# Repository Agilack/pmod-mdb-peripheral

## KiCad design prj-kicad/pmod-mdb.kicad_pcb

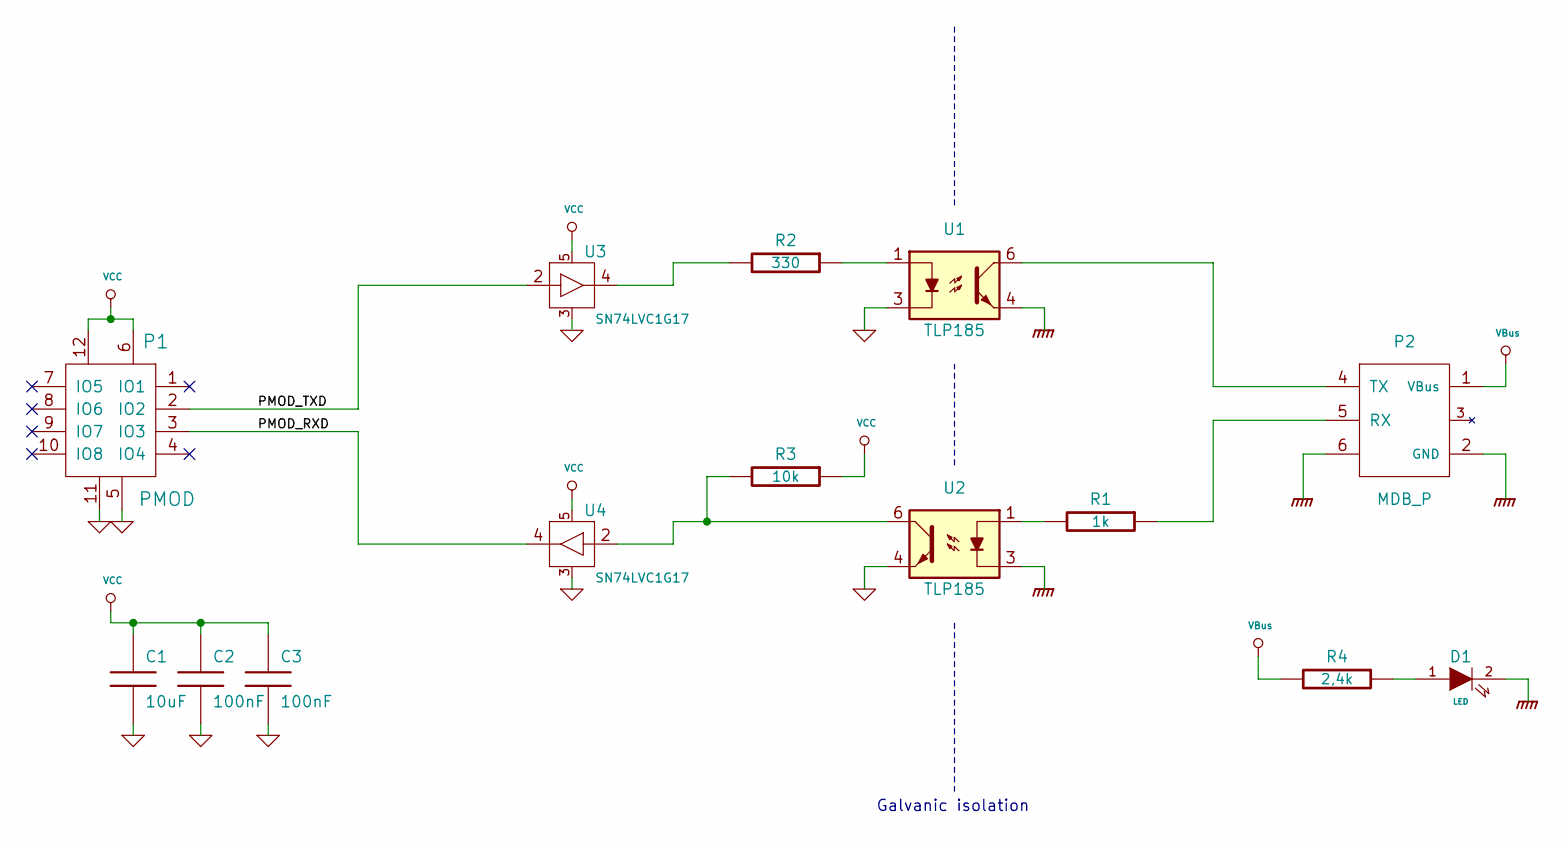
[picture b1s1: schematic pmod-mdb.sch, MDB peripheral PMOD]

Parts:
C1: 10uF; SMD0805
C2, C3: 100nF; SMD0603
D1: LED; SMD0805
P1: PMOD; CONN_PMOD-Male
P2: MDB_P; CONN_64900621122
R1: 1k; SMD0603
R2: 330; SMD0603
R3: 10k; SMD0603
R4: 2,4k; SMD0603
U1, U2: TLP185; SOP6-4
U3, U4: SN74LVC1G17; SOT23-5

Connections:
/PMOD_RXD: P1.3 (IO3), U4.4 (Y)
/PMOD_TXD: P1.2 (IO2), U3.2 (A)
GND: C1.2, C2.2, C3.2, P1.5, P1.11, U1.3, U2.4, U3.3, U4.3
GNDBUS: D1.2 (K), P2.2 (GND), P2.6, U1.4, U2.3
unnamed: D1.1 (A), R4.1
unnamed: P2.4 (TX), U1.6
unnamed: P2.5 (RX), R1.1
unnamed: R1.2, U2.1
unnamed: R2.1, U1.1
unnamed: R2.2, U3.4 (Y)
unnamed: R3.2, U2.6, U4.2 (A)
VBus: P2.1 (VBus), R4.2
VCC: C1.1, C2.1, C3.1, P1.6, P1.12, R3.1, U3.5, U4.5

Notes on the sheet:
Galvanic isolation

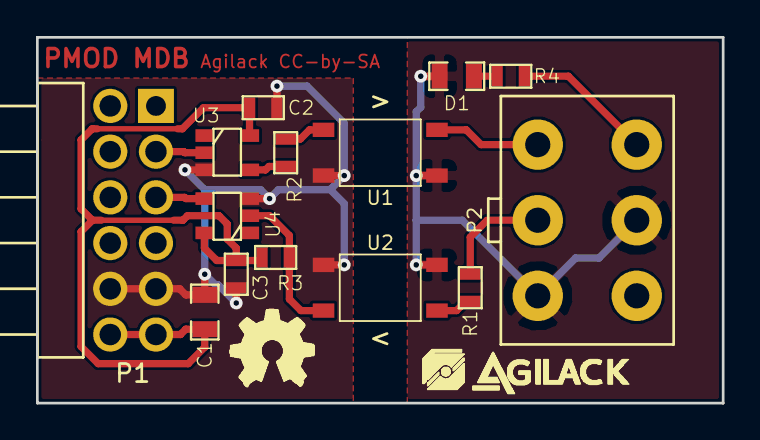
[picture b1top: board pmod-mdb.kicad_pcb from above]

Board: 2 copper layers, 38.1 x 20.3 mm, 16 parts (0 on the bottom side), 13 nets.

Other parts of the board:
agilack-11.5: 450px; logo-agilack-11.5
ohw_logo: VAL**; logo-ohw

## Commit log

2020-04-22 = ADD: Create schematic
2020-04-23 = ADD: Generate netlist and create first board routing

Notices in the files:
prj-kicad/pmod-mdb.kicad_pcb:
Agilack CC-by-SA
